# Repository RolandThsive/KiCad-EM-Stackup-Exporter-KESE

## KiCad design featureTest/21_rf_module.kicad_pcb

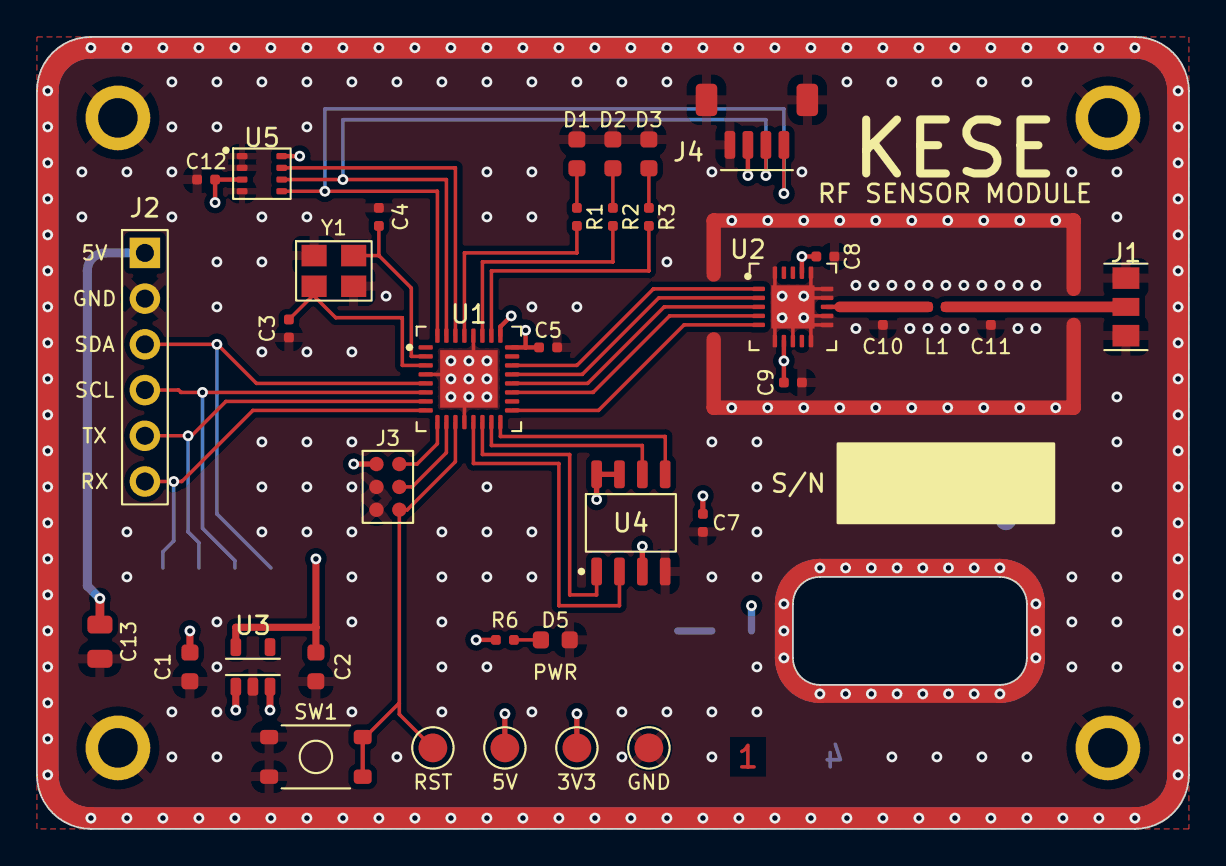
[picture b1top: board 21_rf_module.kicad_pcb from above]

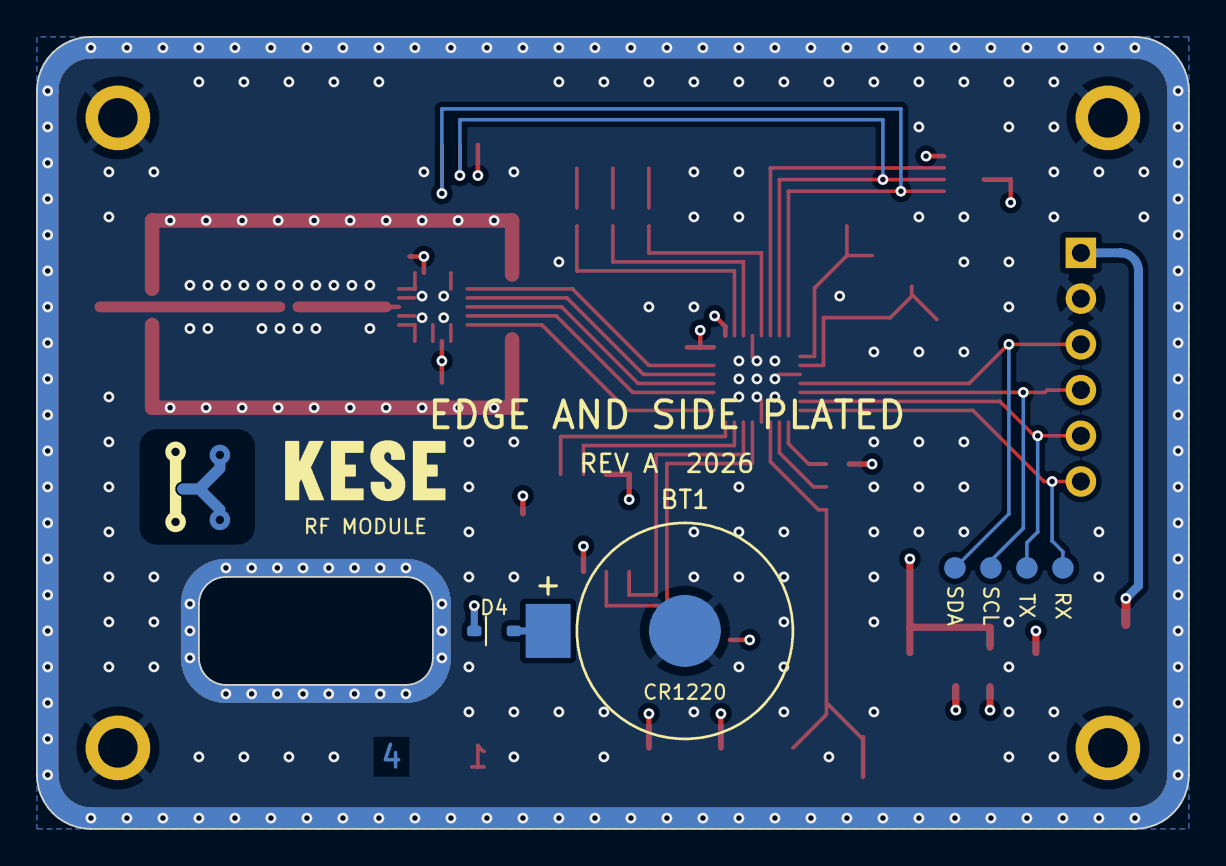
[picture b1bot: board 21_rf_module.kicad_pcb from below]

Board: 4 copper layers, 64.0 x 44.0 mm, 46 parts (6 on the bottom side), 34 nets.

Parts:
BT1: BatteryHolder_CR1220
C1, C2: 0603
C3, C4, C5, C7, C8, C9, C10, C11, C12: 0402
C13: C_0805
D1, D2, D3, D5: 0603
D4: D_SOD-323
H1, H2, H3, H4: MountingHole_2.2mm
J1: Coax_UFL
J2: PinHeader_1x06_P2.54mm
J3: SWD_TagConnect
J4: JST_SH_1x04_P1.0mm
L1: 0402
R1, R2, R3, R6: 0402
SW1: SW_SPST_4.5x3.5mm
TP1, TP2, TP3, TP4: TestPoint_1.6mm
TP5, TP6, TP7, TP8: TestPad_1.2mm
U1: QFN-32_5x5mm
U2: QFN-20_4x4mm
U3: SOT-23-5
U4: SOIC-8_3.9x4.9mm
U5: LGA-8_2.5x2.5mm
Y1: Crystal_3225

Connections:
+3V3: C2.1, C5.1, C7.1, C8.1, C9.1, C12.2, D4.1, J3.1, J4.2, R6.1, TP3.1, U1.24, U1.25, U2.7, U2.17, U3.5, U4.3, U4.7, U4.8, U5.3, U5.8
+5V: C1.1, C13.1, J2.1, TP2.1, U3.1, U3.3
CS: U1.19, U2.4
FCS: U1.14, U4.1
FMISO: U1.13, U4.2
FMOSI: U1.16, U4.5
FSCK: U1.15, U4.6
GND: BT1.2, C1.2, C2.2, C3.2, C4.1, C5.2, C7.2, C8.2, C9.2, C10.2, C11.2, C12.1, C13.2, D1.1, D2.1, D3.1, D5.2, H1.1, H2.1, H3.1, H4.1, J1.2, J1.3, J2.2, J3.2, J3.3, J4.1, J4.MP, SW1.1, SW1.3, TP4.1, U1.4, U1.12, U1.28, U1.33, U2.6, U2.8, U2.10, U2.11, U2.12, U2.14, U2.15, U2.16, U2.20, U2.21, U3.2, U4.4, U5.1, U5.2, U5.4, Y1.2, Y1.4
INT2: U1.30, U5.7
IRQ: U1.17, U2.5
LED1: R1.2, U1.29
LED2: R2.2, U1.27
LED3: R3.2, U1.26
LEDA1: D1.2, R1.1
LEDA2: D2.2, R2.1
LEDA3: D3.2, R3.1
MISO: U1.20, U2.3
MOSI: U1.21, U2.2
NRST: J3.6, SW1.2, SW1.4, TP1.1, U1.11
PWRLED: D5.1, R6.2
RF: C10.1, L1.1, U2.13
RF2: C11.1, J1.1, L1.2
RX: J2.6, TP8.1, U1.8
SCK: U1.22, U2.1
SCL: J2.4, TP6.1, U1.6
SCL2: J4.4, U1.32, U5.5
SDA: J2.3, TP5.1, U1.5
SDA2: J4.3, U1.31, U5.6
SWCLK: J3.5, U1.10
SWDIO: J3.4, U1.9
TX: J2.5, TP7.1, U1.7
VBAT: BT1.1, D4.2
XIN: C3.1, U1.3, Y1.1
XOUT: C4.2, U1.2, Y1.3
